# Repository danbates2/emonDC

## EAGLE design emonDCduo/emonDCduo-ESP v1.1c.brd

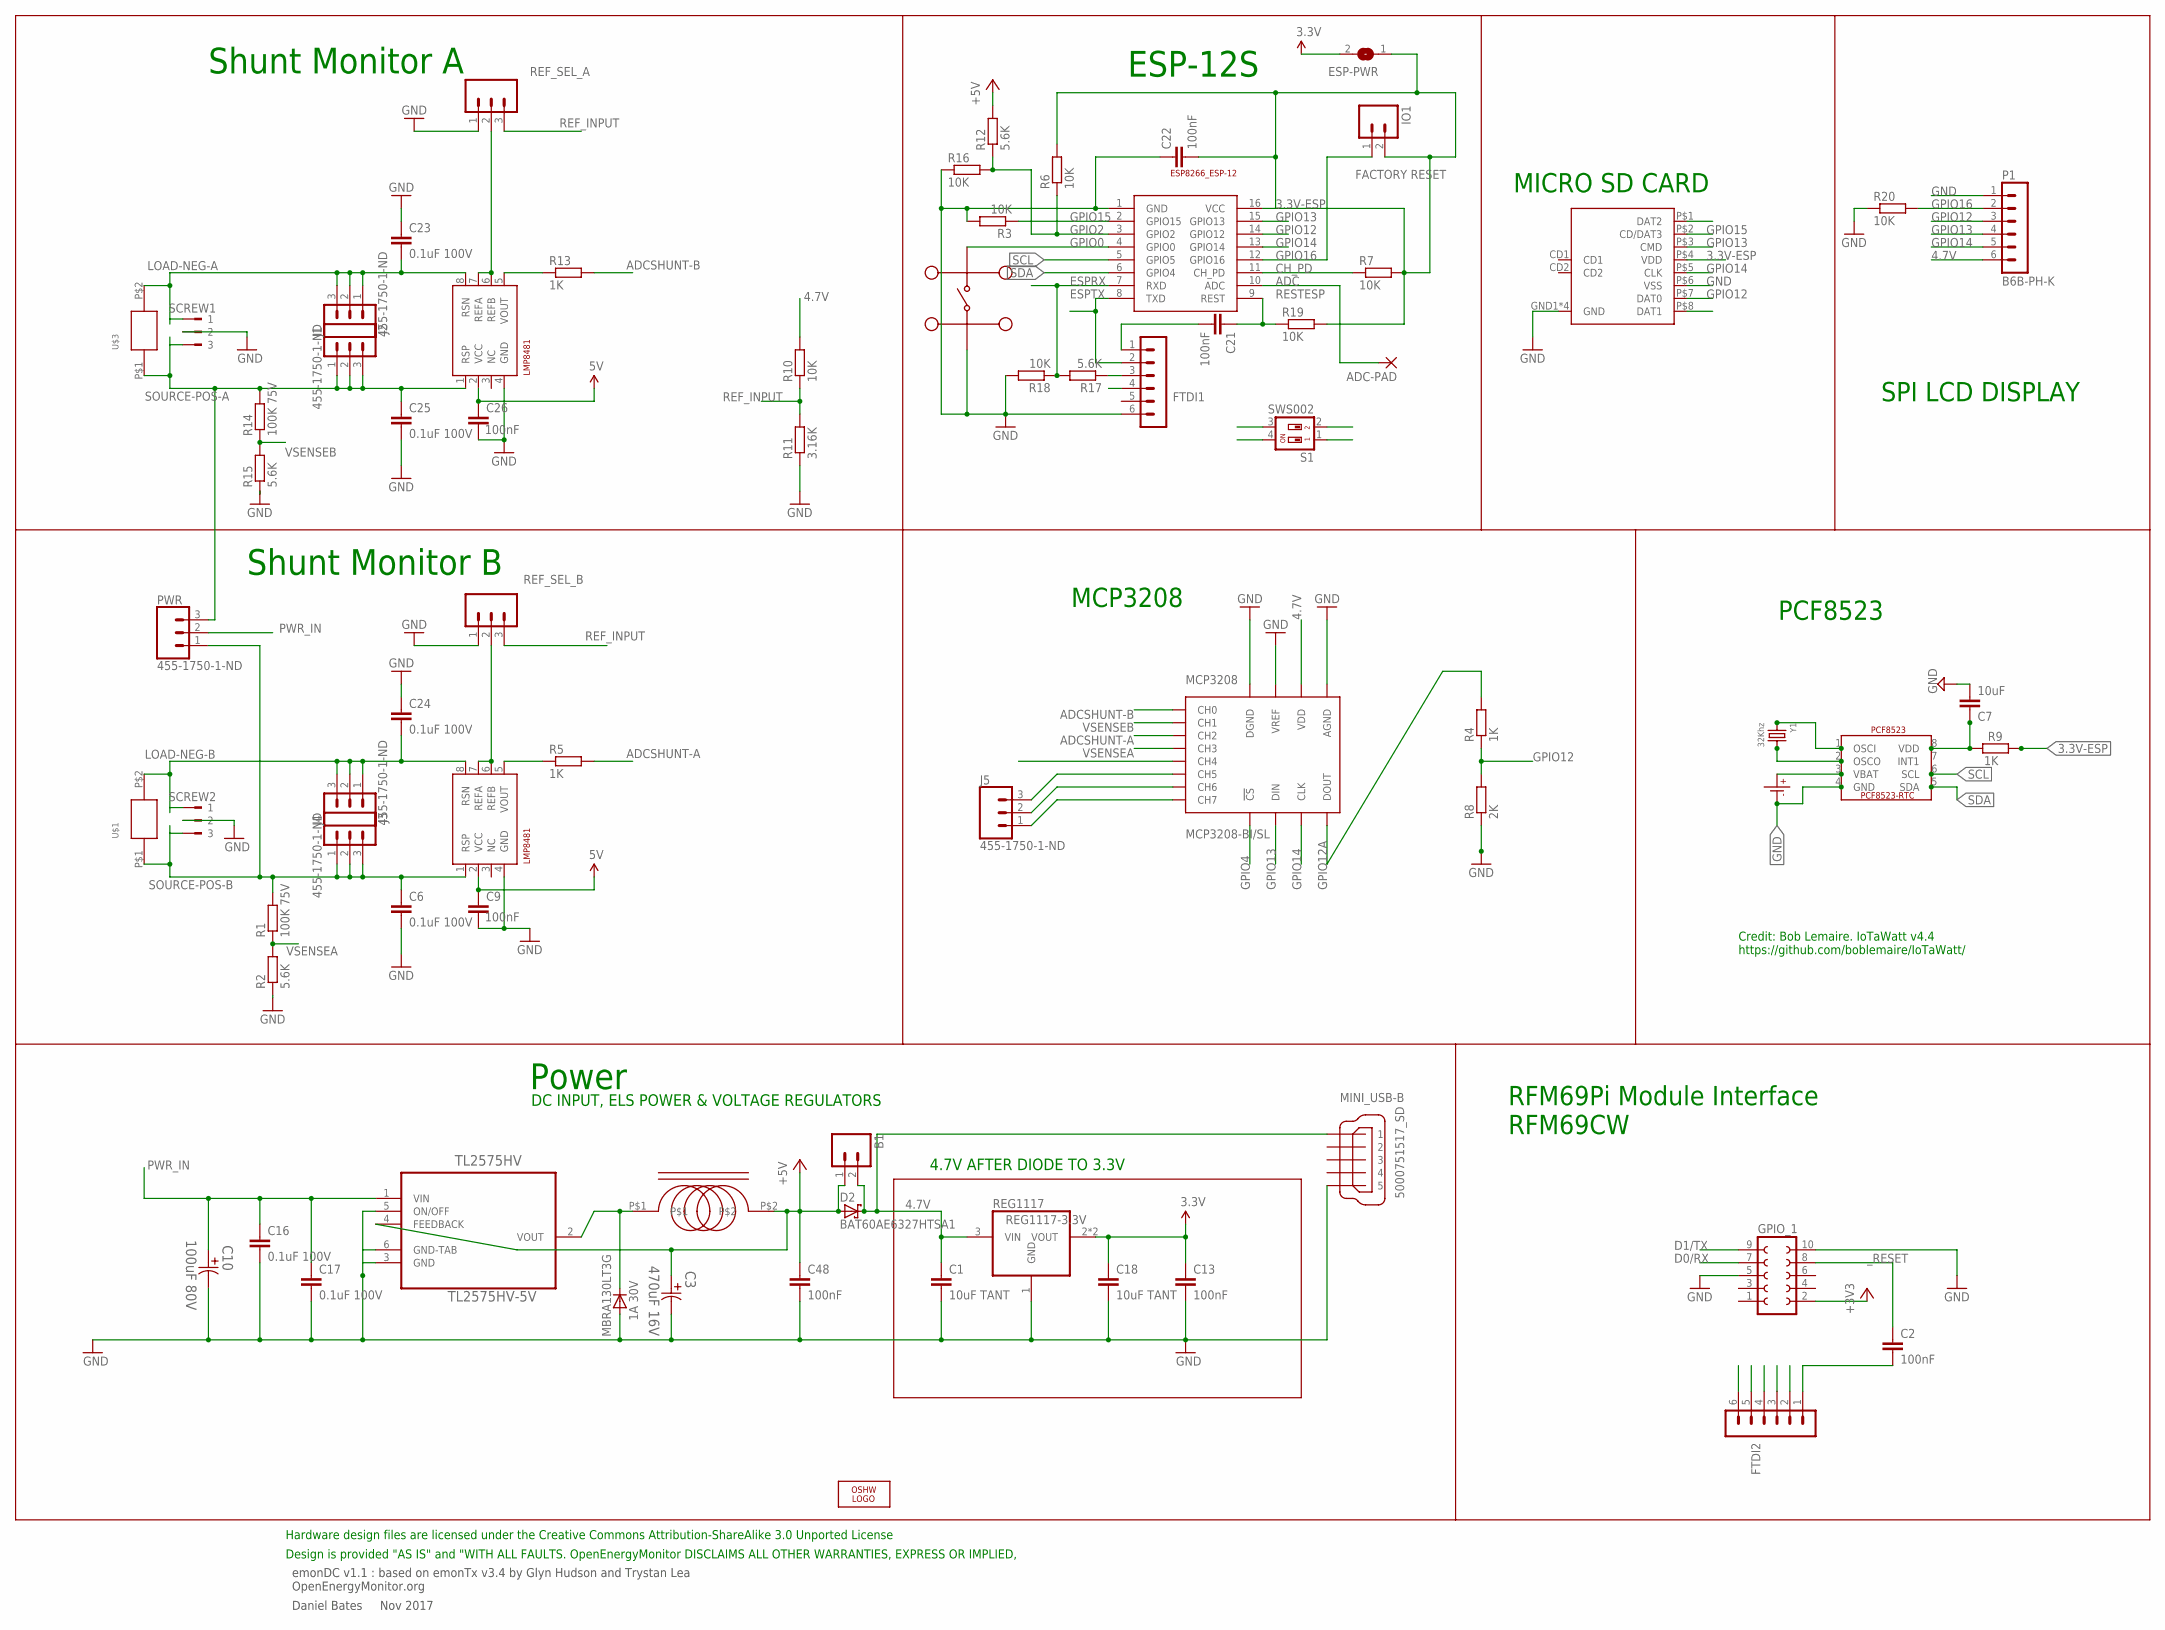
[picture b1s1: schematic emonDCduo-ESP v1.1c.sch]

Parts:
ADC-PAD: 2,15/1,0
B1: M02PTH; 1X02
C1, C18: 10uF TANT; C0603
C2, C13, C21, C22, C48: 100nF; C0603
C3: 470uF 16V; CAPAE830X1050N
C6, C23, C24, C25: 0.1uF 100V; C0603; MPN C1608X7S2A104K080AB
C7: 10uF; C0603
C9, C26: 100nF; C0603; MPN C1608X7S2A104K080AB
C10: 100uF 80V; CAPAE1350X1400N
C16, C17: 0.1uF 100V; C0603
CR1220: CR1220SMD
D1: MBRA130LT3G; DO-214; MPN MBRA130LT3G
D2: BAT60AE6327HTSA1; SOD323_ST
ESP-12: ESP8266_ESP-12; ESP8266-ESP12
ESP-PWR: SJ
FTDI1, FTDI2: FTDI; MA06-1
GPIO_1: FE05-2
I1: 330uH; SRR0603-331KL; MPN SRR0603-331KL
IO1: M02PTH; 1X02
J1, J2, J3, J4, J5: 455-1750-1-ND; 1X03
LOGO1: OSHW_LOGO_6MILX0200-NT; OSHW_6X200_NOTEXT
MC2: MC32882; SWITCH_TACT_MULTICOMP
MCP3208: MCP3208-BI/SL; SOIC16
MINI_USB-B: 5000751517_SD
P1: B6B-PH-K
PCF8523: PCF8523_RTC; SOIC_8
PWR: 455-1750-1-ND; 1X03
R1, R14: 100K 75V; R0603; MPN MCWR06X1003FTL
R2, R15: 5.6K; R0603; MPN MCWR06X5901FTL
R3, R6, R7, R16, R18, R19, R20: 10K; R0603
R4: 1K; R0603; MPN MCWR06X5901FTL
R5, R9, R13: 1K; R0603
R8: 2K; R0603; MPN MCWR06X5901FTL
R10: 10K; 0309/12
R11: 3.16K; 0309/12
R12, R17: 5.6K; R0603
REF_SEL_A: 455-1750-1-ND; 1X03; MPN 2212S-02SG-85
REF_SEL_B: 455-1750-1-ND; 1X03; MPN 2212S-02SG-85
REG1117: REG1117-3.3V; SOT223
S1: SWS002; SMS-002
SCREW1, SCREW2: 180-3
SHUNTMON-A: LMP8481; S-PDSO-G08; MPN LMP8481MME-S/NOPB
SHUNTMON-B: LMP8481; S-PDSO-G08; MPN LMP8481MME-H/NOPB
TL2575HV: TL2575HV-5V; TO-263; MPN LM2575HVS-15/NOPB
U$1, U$3: EBW_SERIES_10.5MM
U$2: MOLEX_MICRO_SD_1040310811; MOLEX_MICROSD_EXPOSED
Y1: 32Khz; CRYSTAL_8X3.8

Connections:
3.3V: C13.1, C18.1, ESP-PWR.2, GPIO_1.2, REG1117.2 (VOUT), REG1117.4 (VOUT)
3.3V-ESP: C22.2, ESP-12.16 (VCC), ESP-PWR.1, IO1.2, R6.2, R7.2, R9.2, R19.2, U$2.P$4 (VDD)
4.7V: B1.2, C1.1, C9.1, C26.1, D2.C, FTDI1.4, FTDI2.4, MCP3208.16 (VDD), MINI_USB-B.VBUS (1), P1.6, R10.2, REG1117.3 (VIN), SHUNTMON-A.2 (VCC), SHUNTMON-B.2 (VCC)
+5V: B1.1, C3.1, C48.1, D2.A, I1.P$2, R12.2, TL2575HV.4 (FEEDBACK)
ADC: ADC-PAD.1, ESP-12.10 (ADC)
ADCSHUNT-A: MCP3208.3 (CH2), R5.2
ADCSHUNT-B: MCP3208.1 (CH0), R13.2
CH_PD: ESP-12.11 (CH_PD), R7.1
D0/RX: FTDI2.2, GPIO_1.7, S1.2
D1/TX: FTDI2.3, GPIO_1.9, S1.1
ESPRX: ESP-12.7 (RXD), R17.2, R18.1, S1.4
ESPTX: ESP-12.8 (TXD), FTDI1.2, S1.3
GND: C1.2, C3.2, C6.2, C7.2, C9.2, C10.2, C13.2, C16.2, C17.2, C18.2, C22.1, C23.1, C24.1, C25.2, C26.2, C48.2, CR1220.P- (P$-), D1.P$2 (A), ESP-12.1 (GND), FTDI1.6, FTDI2.6, GPIO_1.5, GPIO_1.10, MC2.P$1, MC2.P$2, MCP3208.9 (DGND), MCP3208.14 (AGND), MCP3208.15 (VREF), MINI_USB-B.GND1 (5), MINI_USB-B.GND2 (5), MINI_USB-B.GND3 (5), P1.1, PCF8523.4 (GND), R2.1, R3.2, R8.1, R11.1, R15.1, R16.1, R18.2, R20.1, REF_SEL_A.1, REF_SEL_B.1, REG1117.1 (GND), SCREW1.2, SCREW2.2, SHUNTMON-A.4 (GND), SHUNTMON-B.4 (GND), TL2575HV.3 (GND), TL2575HV.5 (ON/OFF), TL2575HV.6 (GND-TAB), U$2.GND1 (GND), U$2.GND2 (GND), U$2.GND3 (GND), U$2.GND4 (GND), U$2.P$6 (VSS)
GPIO0: ESP-12.4 (GPIO0), MC2.P$3, MC2.P$4
GPIO2: ESP-12.3 (GPIO2), R6.1, R12.1, R16.2
GPIO4: MCP3208.10 (!CS)
GPIO12: ESP-12.14 (GPIO12), P1.3, R4.1, R8.2, U$2.P$7 (DAT0)
GPIO12A: MCP3208.12 (DOUT), R4.2
GPIO13: ESP-12.15 (GPIO13), MCP3208.11 (DIN), P1.4, U$2.P$3 (CMD)
GPIO14: ESP-12.13 (GPIO14), MCP3208.13 (CLK), P1.5, U$2.P$5 (CLK)
GPIO15: ESP-12.2 (GPIO15), R3.1, U$2.P$2 (CD/DAT3)
GPIO16: ESP-12.12 (GPIO16), IO1.1, P1.2, R20.2
IND: D1.P$1 (C), I1.P$1, TL2575HV.2 (VOUT)
LOAD-NEG-A: C23.2, J1.1, J1.2, J1.3, SCREW1.1, SHUNTMON-A.8 (RSN), U$3.P$2
LOAD-NEG-B: C24.2, J4.1, J4.2, J4.3, SCREW2.1, SHUNTMON-B.8 (RSN), U$1.P$2
unnamed: J5.3, MCP3208.6 (CH5)
unnamed: R13.1, SHUNTMON-A.5 (VOUT)
unnamed: J5.2, MCP3208.7 (CH6)
unnamed: R5.1, SHUNTMON-B.5 (VOUT)
unnamed: J5.1, MCP3208.8 (CH7)
unnamed: C7.1, PCF8523.8 (VDD), R9.1
unnamed: C21.2, FTDI1.1
unnamed: FTDI1.3, R17.1
unnamed: CR1220.P+ (P$+), PCF8523.3 (VBAT)
unnamed: PCF8523.2 (OSCO), Y1.P$4 (2)
unnamed: PCF8523.1 (OSCI), Y1.P$1 (1)
unnamed: C2.2, FTDI2.1
PWR_IN: C10.1, C16.1, C17.1, PWR.2, TL2575HV.1 (VIN)
REF_A_INPUT: REF_SEL_A.2, SHUNTMON-A.6 (REFB), SHUNTMON-A.7 (REFA)
REF_B_INPUT: REF_SEL_B.2, SHUNTMON-B.6 (REFB), SHUNTMON-B.7 (REFA)
REF_INPUT: MCP3208.5 (CH4), R10.1, R11.2, REF_SEL_A.3, REF_SEL_B.3
RESTESP: C21.1, ESP-12.9 (REST), R19.1
SCL: ESP-12.5 (GPIO5), PCF8523.6 (SCL)
SDA: ESP-12.6 (GPIO4), PCF8523.5 (SDA)
SOURCE-POS-A: C25.1, J2.1, J2.2, J2.3, PWR.3, R14.2, SCREW1.3, SHUNTMON-A.1 (RSP), U$3.P$1
SOURCE-POS-B: C6.1, J3.1, J3.2, J3.3, PWR.1, R1.2, SCREW2.3, SHUNTMON-B.1 (RSP), U$1.P$1
VSENSEA: MCP3208.4 (CH3), R1.1, R2.2
VSENSEB: MCP3208.2 (CH1), R14.1, R15.2
_RESET: C2.1, GPIO_1.8

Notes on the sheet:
emonDC v1.1 : based on emonTx v3.4 by Glyn Hudson and Trystan Lea OpenEnergyMonitor.org
Daniel Bates Nov 2017
Power
Design is provided "AS IS" and "WITH ALL FAULTS. OpenEnergyMonitor DISCLAIMS ALL OTHER WARRANTIES, EXPRESS OR IMPLIED,
Hardware design files are licensed under the Creative Commons Attribution-ShareAlike 3.0 Unported License
DC INPUT, ELS POWER & VOLTAGE REGULATORS
Shunt Monitor B
Shunt Monitor A
FACTORY RESET
ESP-12S
MICRO SD CARD
RFM69Pi Module Interface RFM69CW
4.7V AFTER DIODE TO 3.3V
MCP3208
PCF8523
Credit: Bob Lemaire. IoTaWatt v4.4 https://github.com/boblemaire/IoTaWatt/
SPI LCD DISPLAY

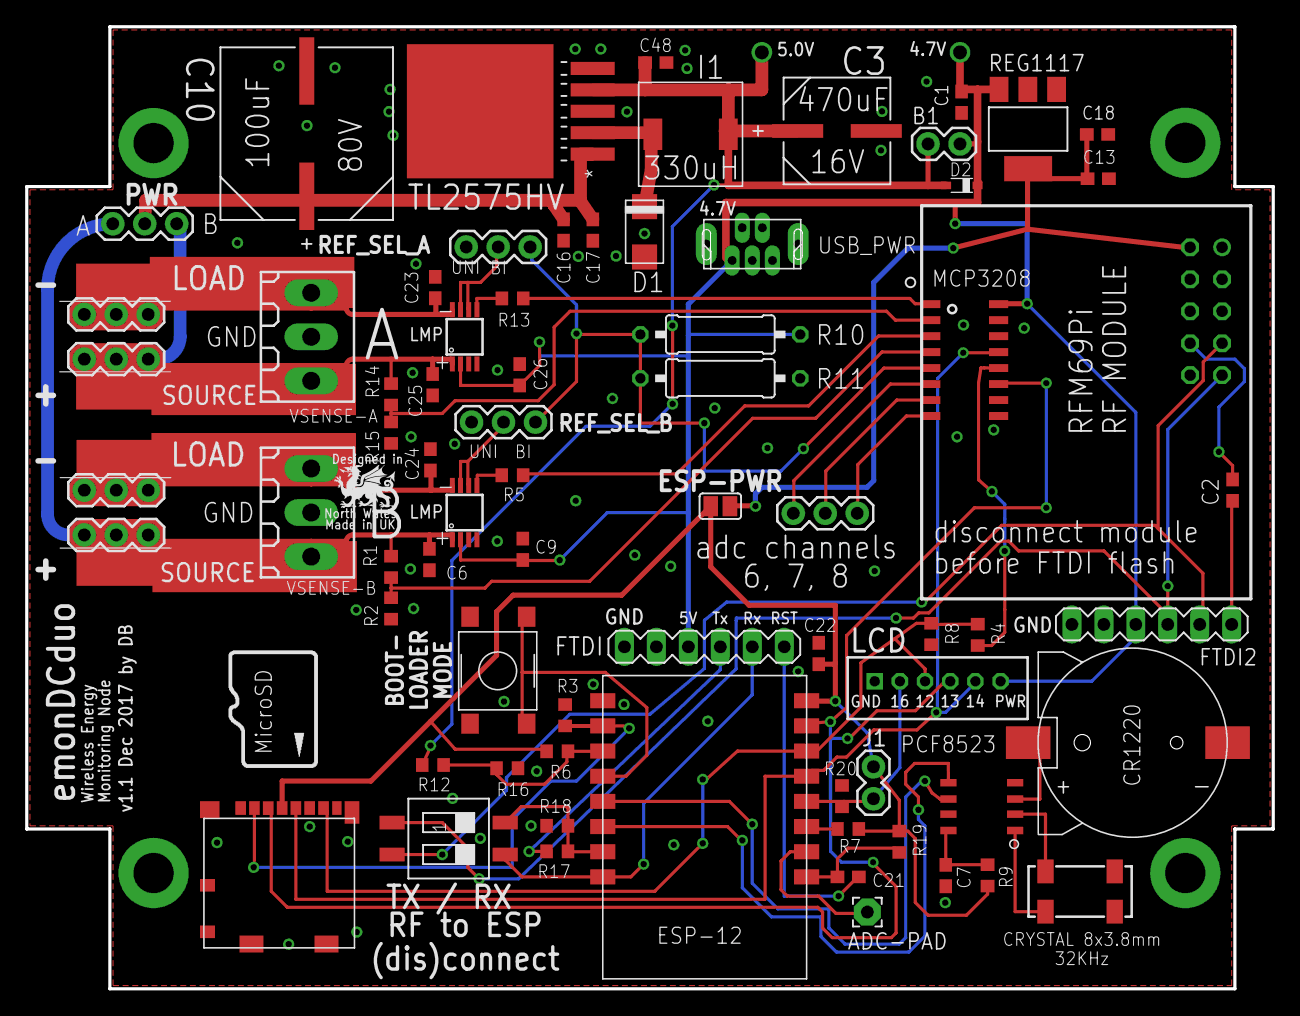
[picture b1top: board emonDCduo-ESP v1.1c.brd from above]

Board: 2 copper layers, 99.1 x 76.5 mm, 75 parts (1 on the bottom side), 48 nets.

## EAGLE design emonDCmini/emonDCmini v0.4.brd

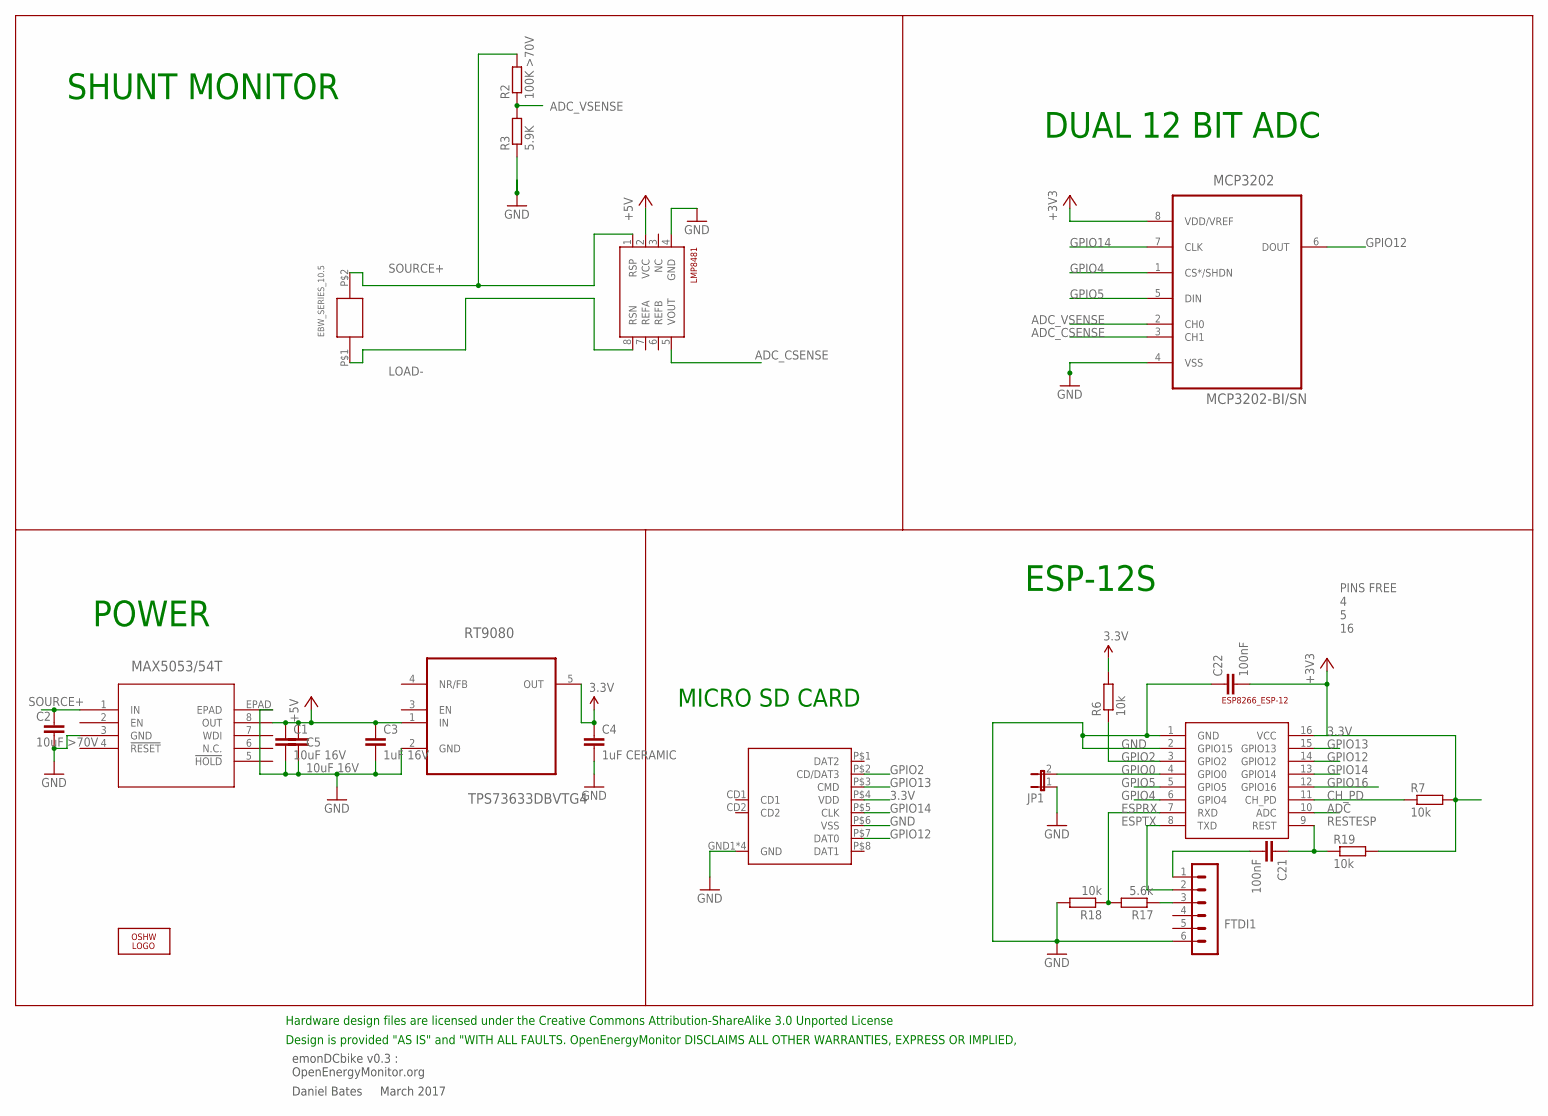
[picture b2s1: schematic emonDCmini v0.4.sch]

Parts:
C1, C5: 10uF 16V; C0603
C2: 10uF >70V; C0603
C3: 1uF 16V; C0603
C4: 1uF CERAMIC; C0603
C21, C22: 100nF; C0603
EBW_SERIES_10.5: EBW_SERIES_10.5MM
ESP-12: ESP8266_ESP-12; ESP8266-ESP12
FTDI1: FTDI-ESP; MA06-1
JP1: JP1E; JP1
LMP8481: LMP8481-H; S-PDSO-G08
LOGO1: OSHW_LOGO_6MILX0200-NT; OSHW_6X200_NOTEXT
MAX5053: MAX5023TASA-T21-0111D_SBE-14-L; 21-0111D_SBE-14-L
MCP3202: MCP3202-BI/SN; SOIC127P600X175-8N
R2: 100K >70V; R0603; MPN MCWR06X1003FTL
R3: 5.9K; R0603; MPN MCWR06X5901FTL
R6, R7, R18, R19: 10k; R0603
R17: 5.6k; R0603
RT9080: TPS73633DBVTG4; SOT95P280X145-5N
U$2: MOLEX_MICRO_SD_1040310811; MOLEX_MICROSD_EXPOSED

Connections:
3.3V: C4.1, C22.2, ESP-12.16 (VCC), MCP3202.8 (VDD/VREF), R6.2, R7.2, R19.2, RT9080.5 (OUT), U$2.P$4 (VDD)
+5V: C1.1, C3.1, C5.1, MAX5053.8 (OUT), RT9080.1 (IN)
ADC: ESP-12.10 (ADC)
ADC_CSENSE: LMP8481.5 (VOUT), MCP3202.3 (CH1)
ADC_VSENSE: MCP3202.2 (CH0), R2.1, R3.2
CH_PD: ESP-12.11 (CH_PD), R7.1
ESPRX: ESP-12.7 (RXD), R17.2, R18.1
ESPTX: ESP-12.8 (TXD), FTDI1.2
GND: C1.2, C2.2, C3.2, C4.2, C5.2, C22.1, ESP-12.1 (GND), ESP-12.2 (GPIO15), FTDI1.6, JP1.1, LMP8481.4 (GND), MAX5053.3 (GND), MAX5053.EPAD, MCP3202.4 (VSS), R3.1, R18.2, RT9080.2 (GND), U$2.GND1 (GND), U$2.GND2 (GND), U$2.GND3 (GND), U$2.GND4 (GND), U$2.P$6 (VSS)
GPIO0: ESP-12.4 (GPIO0), JP1.2
GPIO2: ESP-12.3 (GPIO2), R6.1, U$2.P$2 (CD/DAT3)
GPIO4: ESP-12.6 (GPIO4), MCP3202.1 (CS*/SHDN)
GPIO5: ESP-12.5 (GPIO5), MCP3202.5 (DIN)
GPIO12: ESP-12.14 (GPIO12), MCP3202.6 (DOUT), U$2.P$7 (DAT0)
GPIO13: ESP-12.15 (GPIO13), U$2.P$3 (CMD)
GPIO14: ESP-12.13 (GPIO14), MCP3202.7 (CLK), U$2.P$5 (CLK)
GPIO16: ESP-12.12 (GPIO16)
LOAD-: EBW_SERIES_10.5.P$1, LMP8481.8 (RSN)
unnamed: FTDI1.3, R17.1
RESTESP: C21.1, ESP-12.9 (REST), R19.1
RST: C21.2, FTDI1.1
SOURCE+: C2.1, EBW_SERIES_10.5.P$2, LMP8481.1 (RSP), MAX5053.1 (IN), R2.2

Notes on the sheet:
emonDCbike v0.3 : OpenEnergyMonitor.org
Daniel Bates March 2017
Design is provided "AS IS" and "WITH ALL FAULTS. OpenEnergyMonitor DISCLAIMS ALL OTHER WARRANTIES, EXPRESS OR IMPLIED,
Hardware design files are licensed under the Creative Commons Attribution-ShareAlike 3.0 Unported License
SHUNT MONITOR
ESP-12S
MICRO SD CARD
PINS FREE 4 5 16
POWER
DUAL 12 BIT ADC

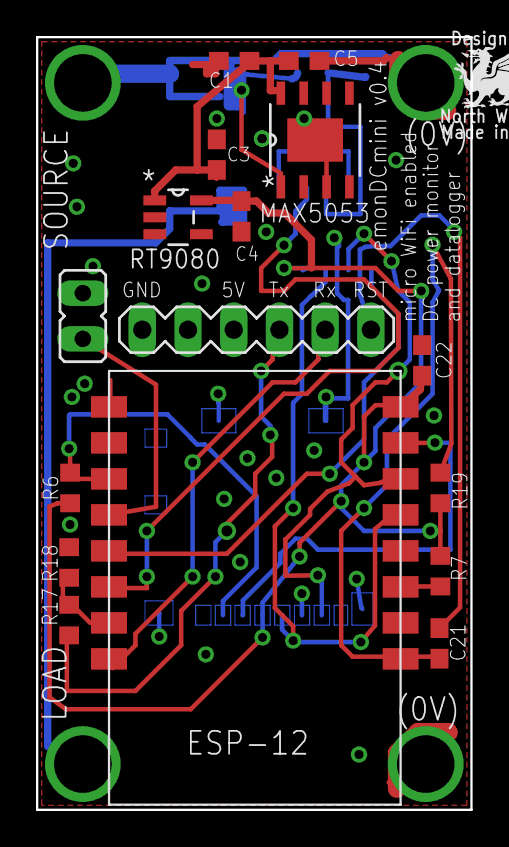
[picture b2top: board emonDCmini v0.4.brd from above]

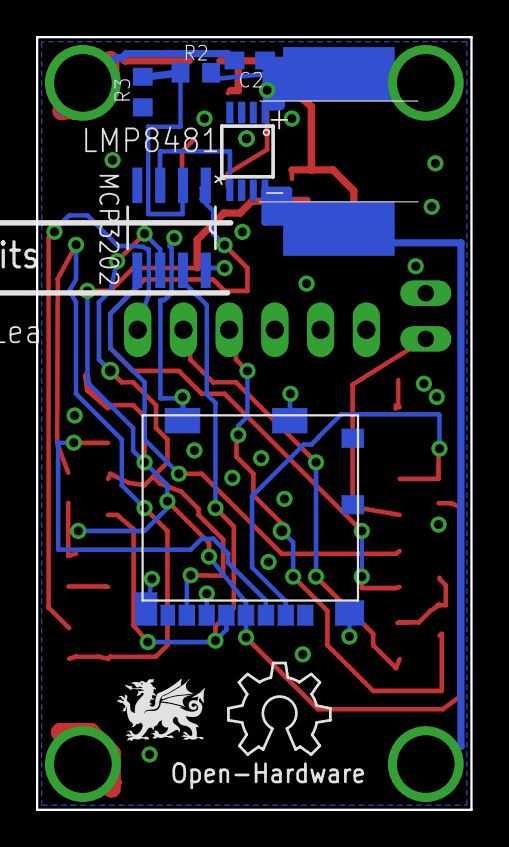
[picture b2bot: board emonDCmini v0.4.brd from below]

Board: 2 copper layers, 24.1 x 42.9 mm, 25 parts (9 on the bottom side), 20 nets.

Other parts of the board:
U$3: DRAGON_LOGO_NOTEXT

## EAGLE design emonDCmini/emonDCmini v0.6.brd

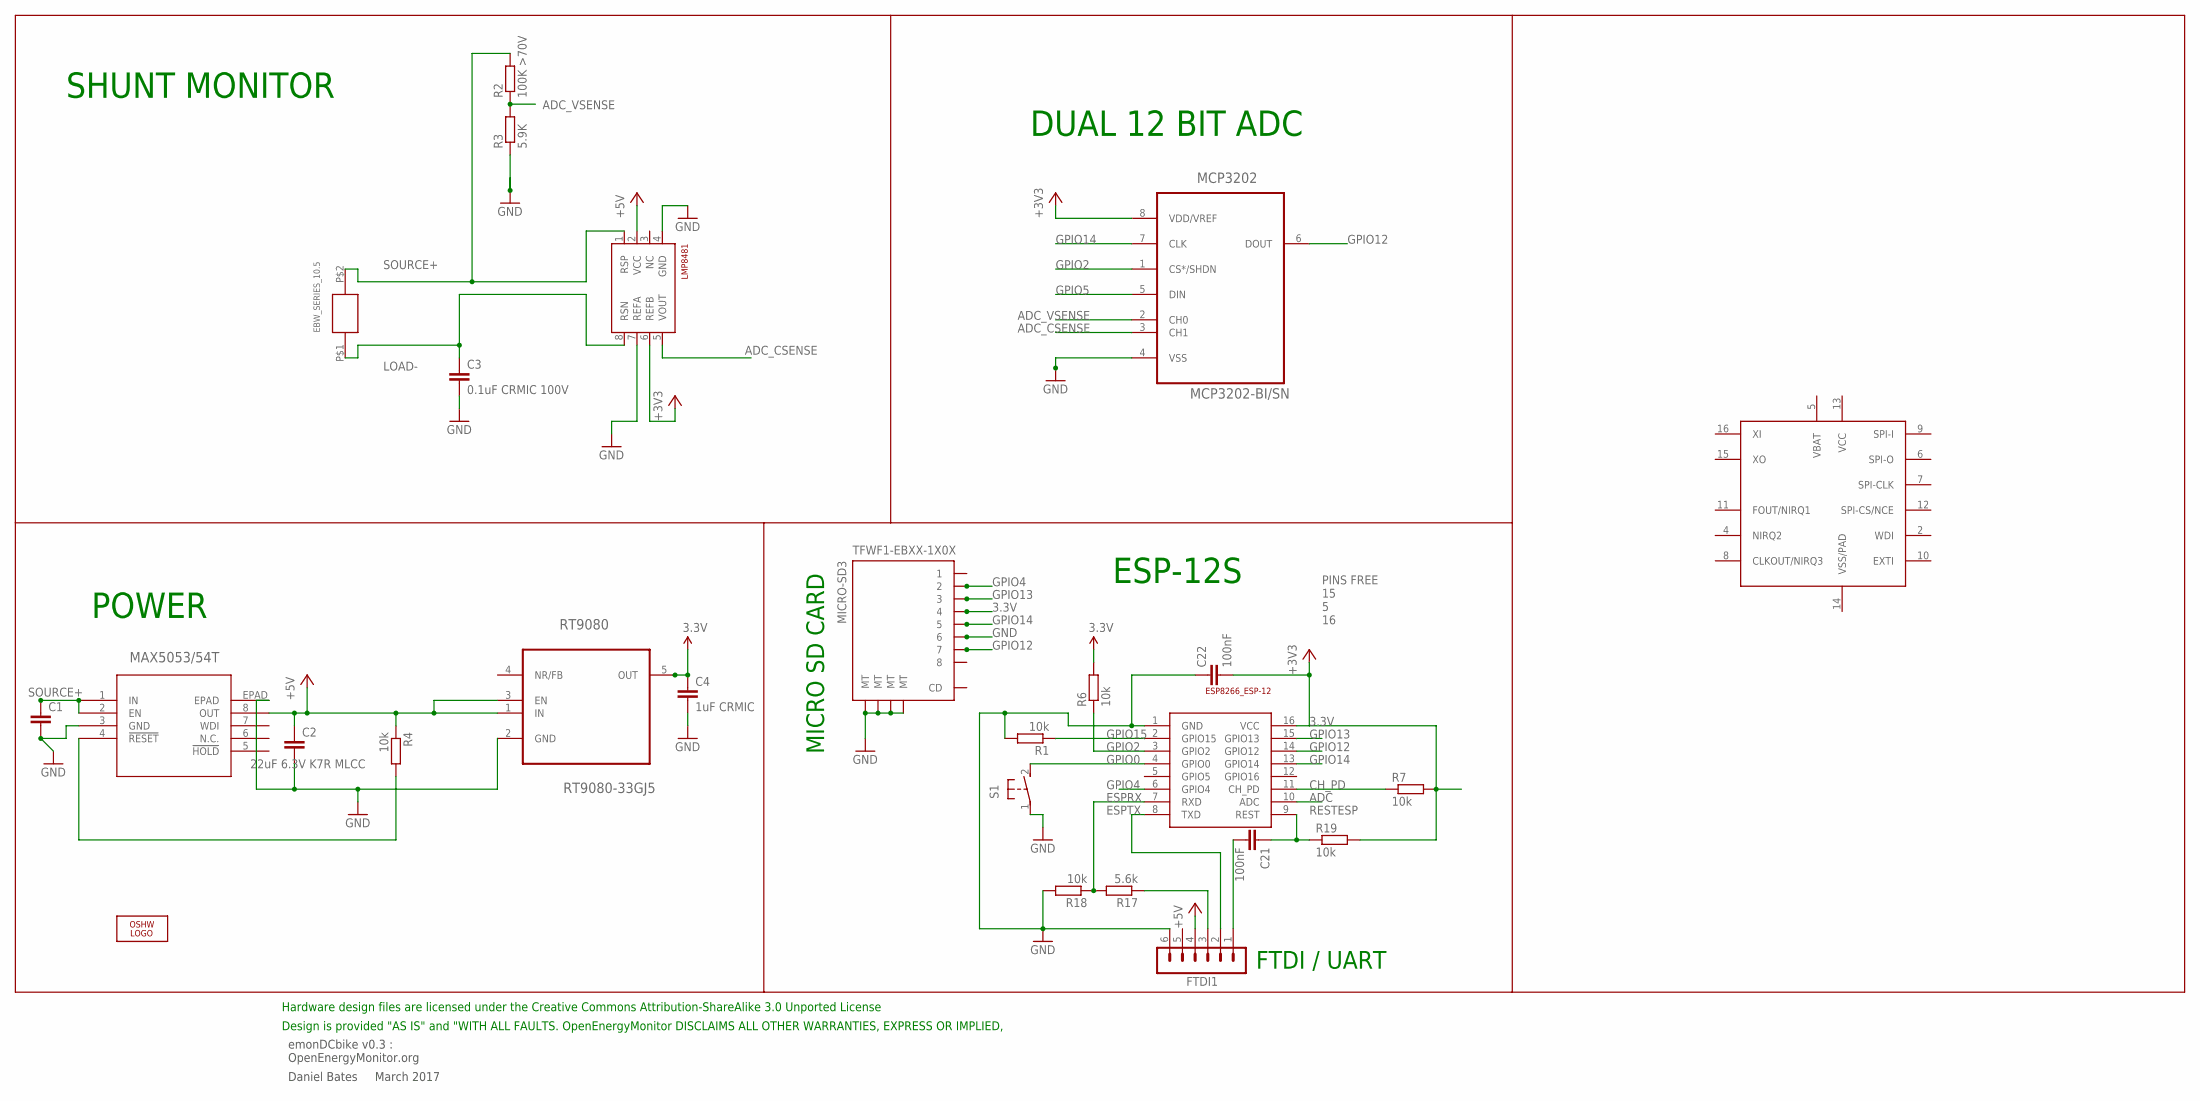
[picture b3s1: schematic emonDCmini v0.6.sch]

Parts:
AB0815: AB0815_RTC; QFN16
C1: C-EUC1206; C1206
C2: 22uF 6.3V K7R MLCC; C1206
C3: 0.1uF CRMIC 100V; C0603
C4: 1uF CRMIC; C0603
C21, C22: 100nF; C0603
EBW_SERIES_10.5: EBW_SERIES_10.5MM
ESP-12: ESP8266_ESP-12; ESP8266-ESP12
FTDI1: FTDI-ESP; MA06-1
LMP8481: LMP8481-H; S-PDSO-G08
LOGO1: OSHW_LOGO_6MILX0200-NT; OSHW_6X200_NOTEXT
MAX5053: MAX5023TASA-T21-0111D_SBE-14-L; 21-0111D_SBE-14-L
MCP3202: MCP3202-BI/SN; SOIC127P600X175-8N
R1, R4, R6, R7, R18, R19: 10k; R0603
R2: 100K >70V; R0603; MPN MCWR06X1003FTL
R3: 5.9K; R0603; MPN MCWR06X5901FTL
R17: 5.6k; R0603
RT9080: RT9080-33GJ5; TSOT-23-5
S1: DTSM-3
TFWF1-EBXX-1X0X: MICRO-SD3; TF-MICRO-SD_PP3*

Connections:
3.3V: C4.1, C22.2, ESP-12.16 (VCC), LMP8481.6 (REFB), MCP3202.8 (VDD/VREF), R6.2, R7.2, R19.2, RT9080.5 (OUT), TFWF1-EBXX-1X0X.4
+5V: C2.1, FTDI1.4, MAX5053.8 (OUT), R4.1, RT9080.1 (IN), RT9080.3 (EN)
ADC: ESP-12.10 (ADC)
ADC_CSENSE: LMP8481.5 (VOUT), MCP3202.3 (CH1)
ADC_VSENSE: MCP3202.2 (CH0), R2.1, R3.2
CH_PD: ESP-12.11 (CH_PD), R7.1
ESPRX: ESP-12.7 (RXD), R17.2, R18.1
ESPTX: ESP-12.8 (TXD), FTDI1.2
GND: C1.2, C2.2, C3.2, C4.2, C22.1, ESP-12.1 (GND), FTDI1.6, LMP8481.4 (GND), LMP8481.7 (REFA), MAX5053.3 (GND), MAX5053.EPAD, MCP3202.4 (VSS), R1.2, R3.1, R18.2, RT9080.2 (GND), S1.1, TFWF1-EBXX-1X0X.6, TFWF1-EBXX-1X0X.MT1 (MT), TFWF1-EBXX-1X0X.MT2 (MT), TFWF1-EBXX-1X0X.MT3 (MT), TFWF1-EBXX-1X0X.MT4 (MT)
GPIO0: ESP-12.4 (GPIO0), S1.2
GPIO2: ESP-12.3 (GPIO2), MCP3202.1 (CS*/SHDN), R6.1
GPIO4: ESP-12.6 (GPIO4), TFWF1-EBXX-1X0X.2
GPIO5: MCP3202.5 (DIN)
GPIO12: ESP-12.14 (GPIO12), MCP3202.6 (DOUT), TFWF1-EBXX-1X0X.7
GPIO13: ESP-12.15 (GPIO13), TFWF1-EBXX-1X0X.3
GPIO14: ESP-12.13 (GPIO14), MCP3202.7 (CLK), TFWF1-EBXX-1X0X.5
GPIO15: ESP-12.2 (GPIO15), R1.1
LOAD-: C3.1, EBW_SERIES_10.5.P$1, LMP8481.8 (RSN)
unnamed: MAX5053.4 (!RESET), R4.2
unnamed: FTDI1.3, R17.1
RESTESP: C21.1, ESP-12.9 (REST), R19.1
RST: C21.2, FTDI1.1
SOURCE+: C1.1, EBW_SERIES_10.5.P$2, LMP8481.1 (RSP), MAX5053.1 (IN), MAX5053.2 (EN), R2.2

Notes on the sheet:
emonDCbike v0.3 : OpenEnergyMonitor.org
Daniel Bates March 2017
Design is provided "AS IS" and "WITH ALL FAULTS. OpenEnergyMonitor DISCLAIMS ALL OTHER WARRANTIES, EXPRESS OR IMPLIED,
Hardware design files are licensed under the Creative Commons Attribution-ShareAlike 3.0 Unported License
SHUNT MONITOR
ESP-12S
MICRO SD CARD
PINS FREE 15 5 16
POWER
DUAL 12 BIT ADC
FTDI / UART

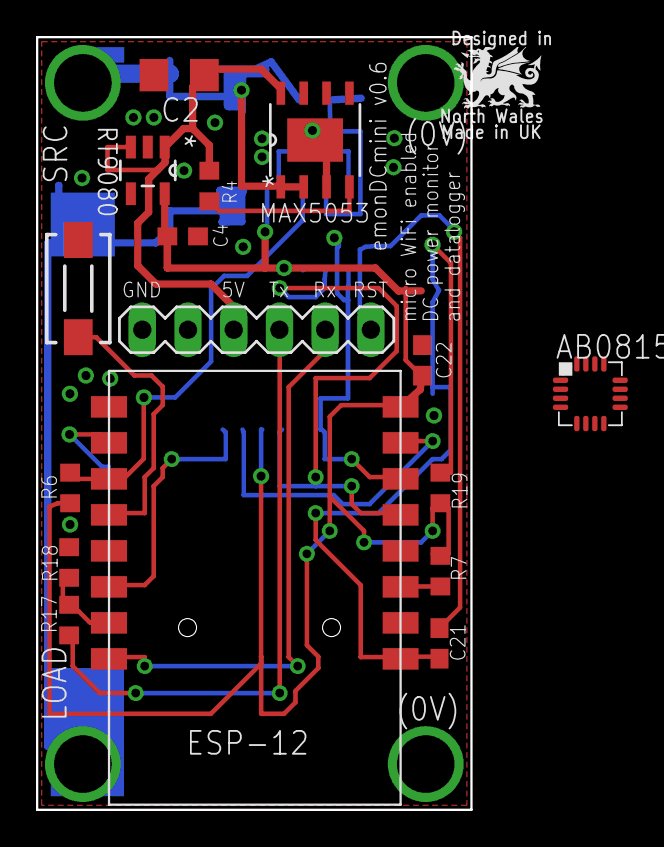
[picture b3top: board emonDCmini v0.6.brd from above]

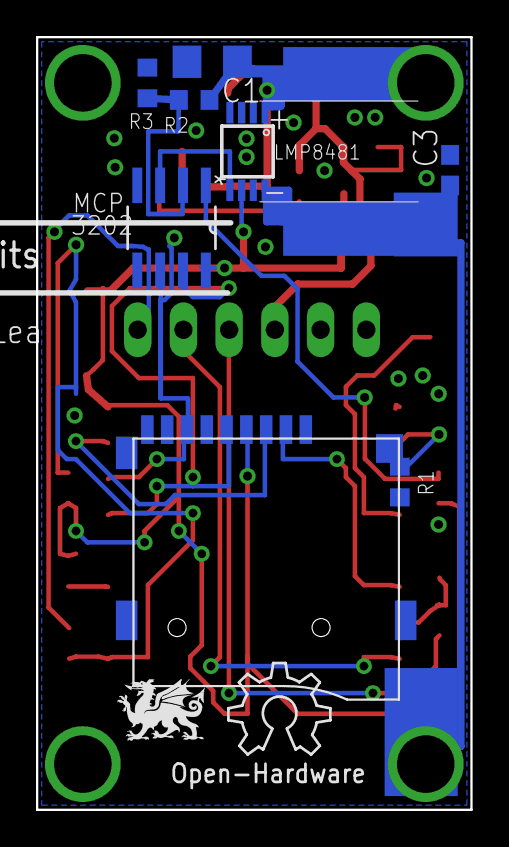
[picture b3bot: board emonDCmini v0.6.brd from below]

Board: 2 copper layers, 24.1 x 42.9 mm, 27 parts (11 on the bottom side), 21 nets.

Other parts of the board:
U$3: DRAGON_LOGO_NOTEXT

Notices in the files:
parts and their libraries:
SparkFun-Connectors: Licensing: CC v3.0 Share-Alike You are welcome to use this library for commercial purposes.
microbuilder: This work is placed in the public domain, and may be freely used for commercial and non-commercial work with the following conditions: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
jst-ph: Copyright (C) 2016, Bob Starr
